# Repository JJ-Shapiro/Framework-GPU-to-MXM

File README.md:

# Framework-GPU-to-MXM
A project to make the first MXM module for the Framework 16.
*Info*
The Framework 16's Expansion bay can't support the size of an MXM module by default, (at least not a type-B module which is bigger than a type a module), but it *can* support it if the back of the GPU expansion slot is pulled out further 

*Disclaimer*
I am not the legal owner of the datasheet describing the footprint of an MXM connector. It is in this repository strictly as a helpful reference for anyone who might desire to use or cross reference it. I will of course remove it at the request of the author.

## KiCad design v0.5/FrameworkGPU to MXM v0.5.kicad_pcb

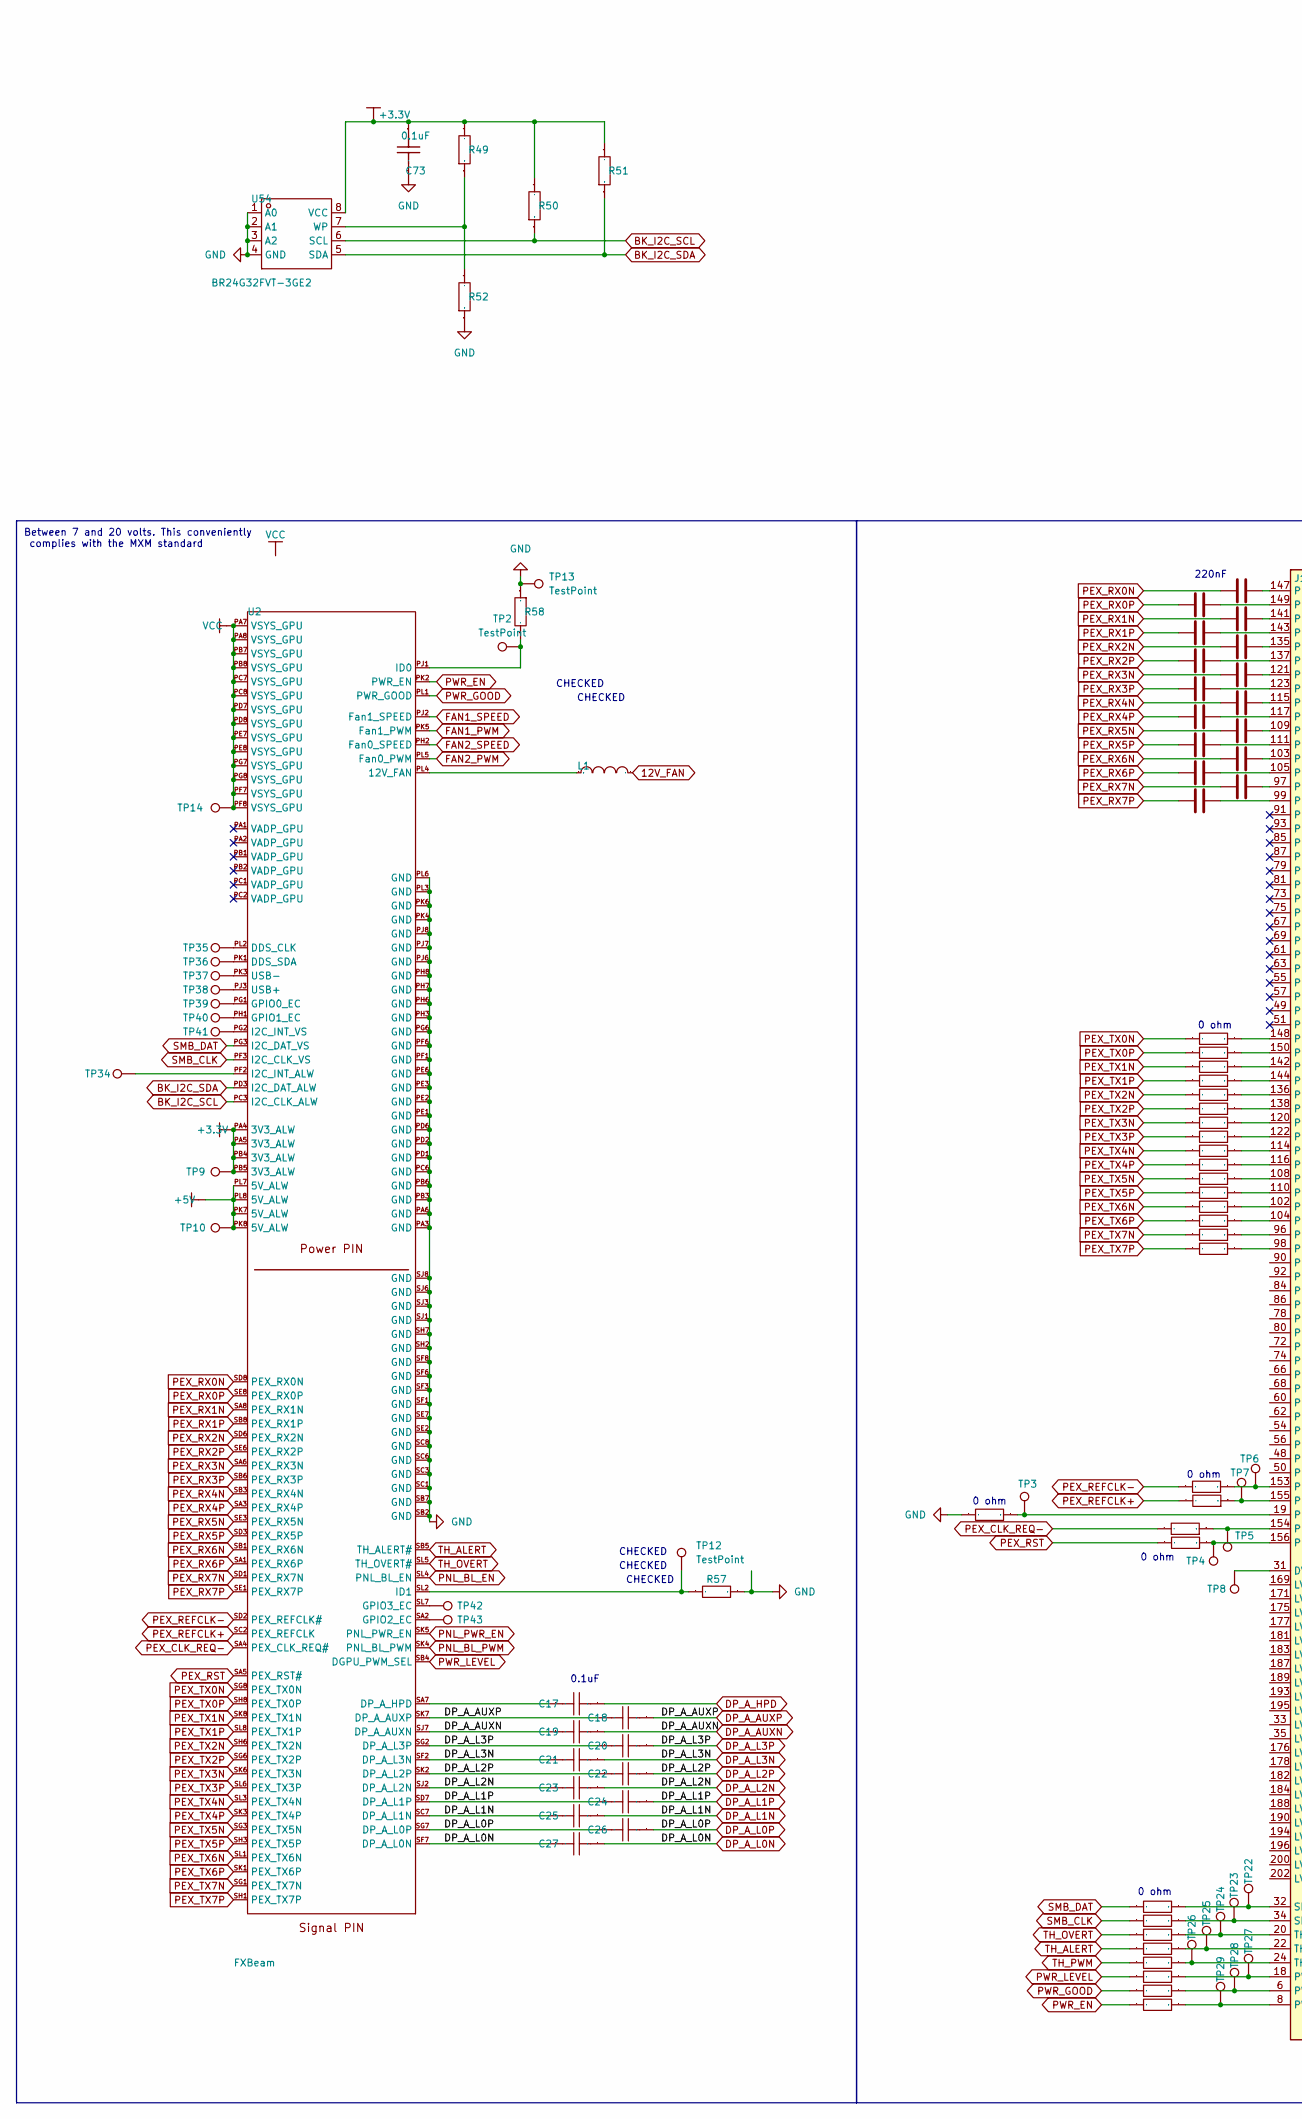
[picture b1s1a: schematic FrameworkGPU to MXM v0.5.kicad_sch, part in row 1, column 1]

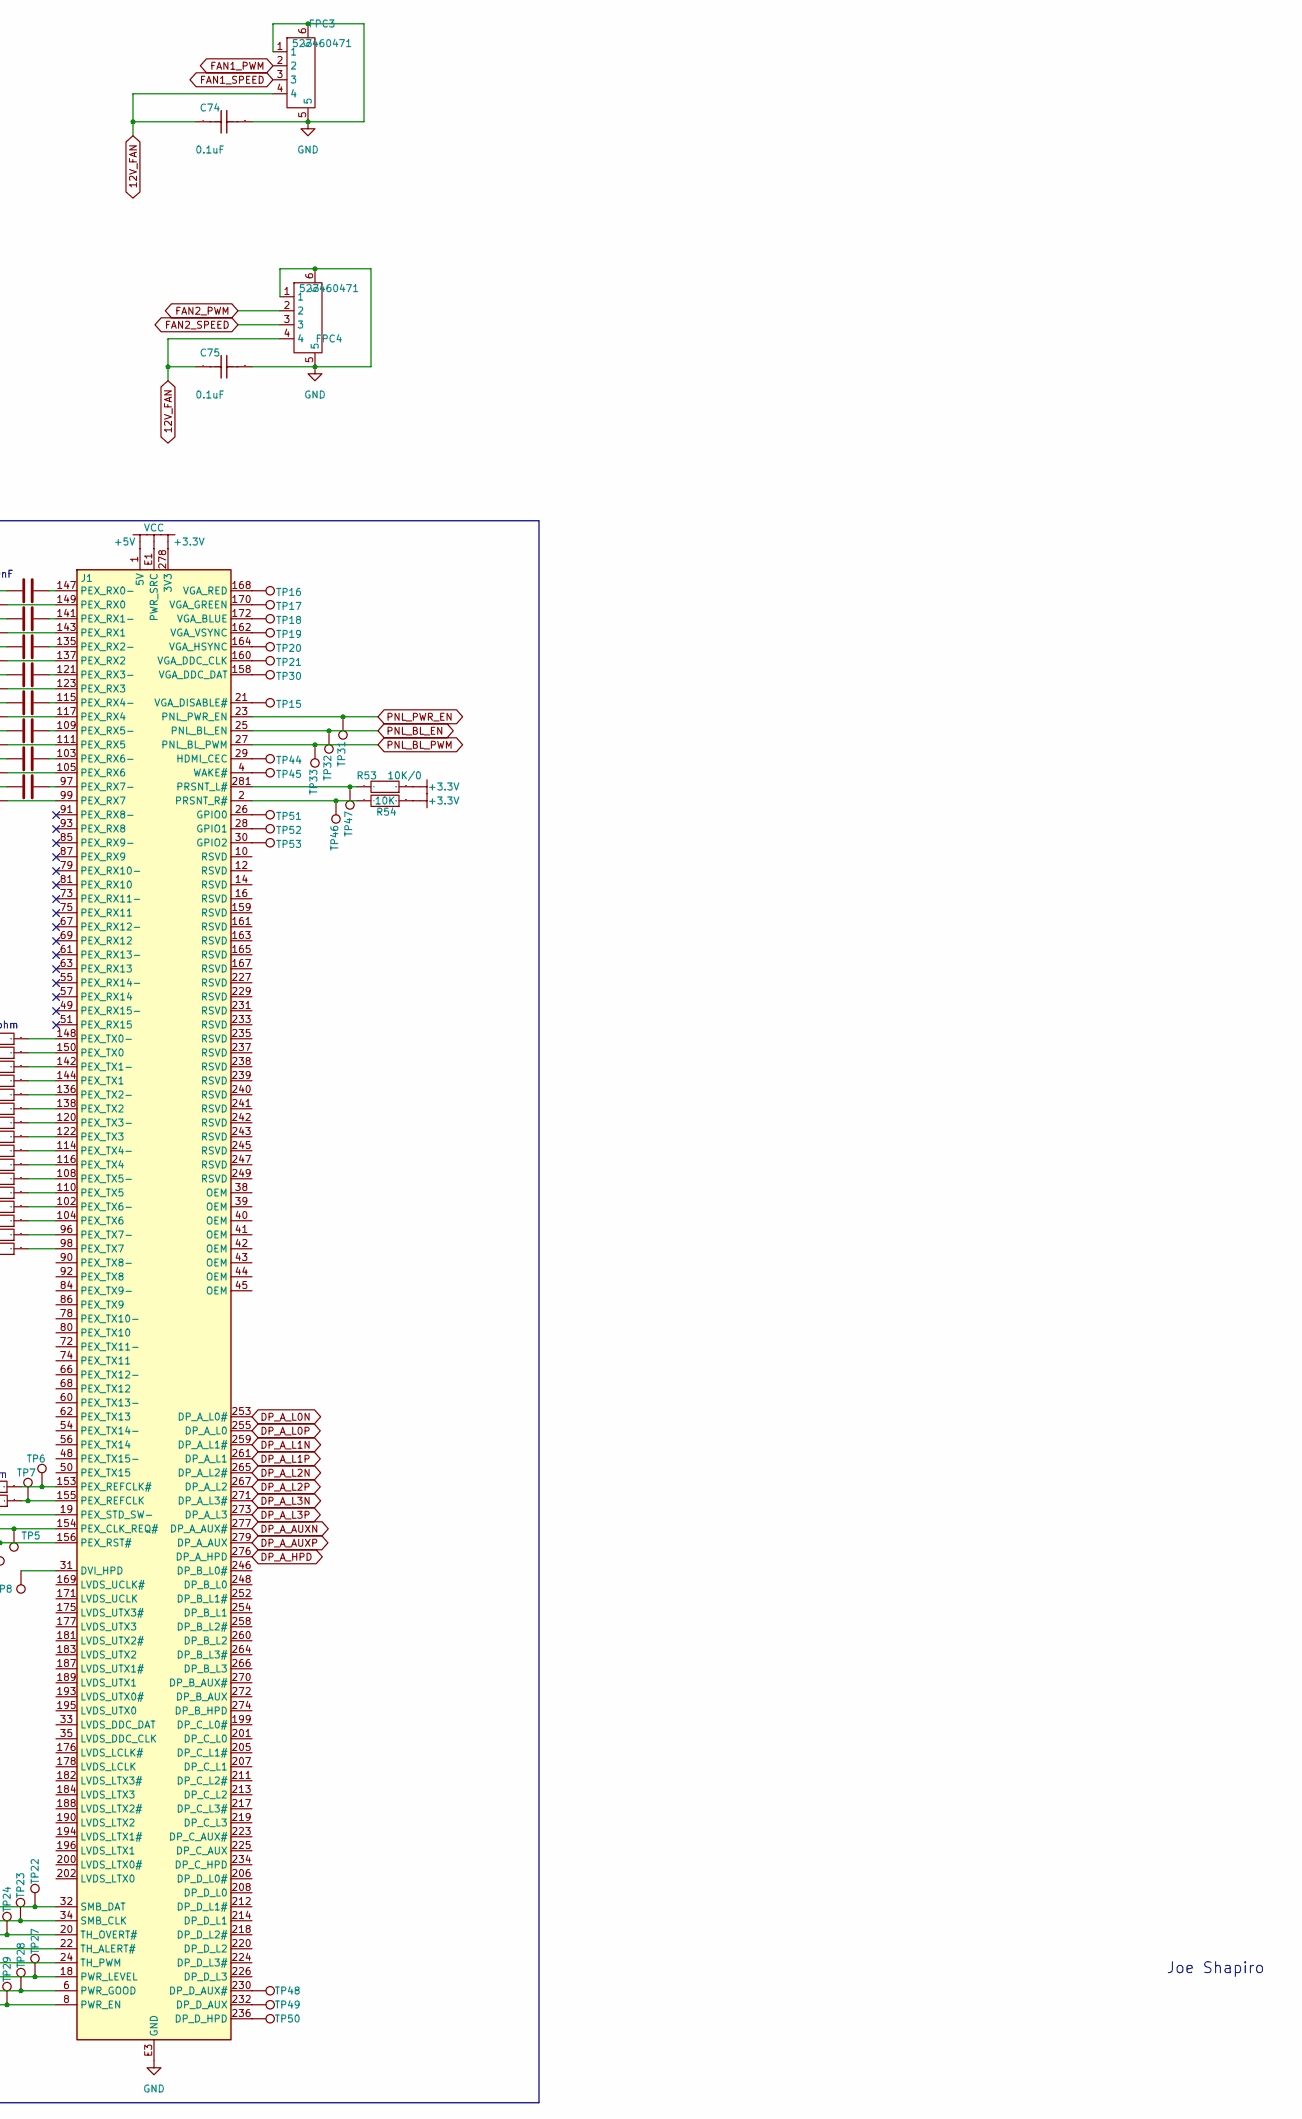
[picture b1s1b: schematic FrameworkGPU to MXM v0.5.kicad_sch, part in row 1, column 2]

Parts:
C1, C2, C3, C4, C5, C6, C7, C8, C9, C10, C11, C12, C13, C14, C15, C16: 220nF; 0603
C17, C18, C19, C20, C21, C22, C23, C24, C25, C26, C27: 100nF; 0603
C73, C74, C75: 0.1uF; 0603
FPC3, FPC4: 527460471; FPC-SMD_4P-P0.50_MOLEX_0527460471; Manufacturer Part 527460471; LCSC Part Name 527460471
J1: MXM3.0; FOXCONN_AS0B826-S55B-7H
L1: 10uH; 0603
R17, R18, R19, R20, R21, R22, R23, R24, R25, R26, R27, R28, R29, R30, R31, R32, R33, R34, R35, R36, R37, R55, R56, R59, R60, R61, R62, R63, R64: 0; 0603
R49, R54: 10K; 0603
R50, R51: 4.7K; 0603
R52: 100K; 0603
R53: 10K/0; 0603
R57, R58: 330K; 0603
TP2, TP3, TP4, TP5, TP6, TP7, TP8, TP9, TP10, TP12, TP13, TP14, TP15, TP16, TP17, TP18, TP19, TP20, TP21, TP22, TP23, TP24, TP25, TP26, TP27, TP28, TP29, TP30, TP31, TP32, TP33, TP34, TP35, TP36, TP37, TP38, TP39, TP40, TP41, TP42, TP43, TP44, TP45, TP46, TP47, TP48, TP49, TP50, TP51, TP52, TP53: TestPoint; TestPoint_Pad_D3.0mm
U2: FXBeam; Expansion Bay FXBeam
U54: BR24G32FVT-3GE2; SOP65P640X120-8N; Manufacturer Part BR24G32FVT-3GE2; LCSC Part Name BR24G32FVT-3GE2

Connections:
+3.3V: C73.1, J1.278 (3V3), J1.280 (3V3), R49.2, R50.2, R51.2, R53.1, R54.1, TP9.1, U2.PA4 (3V3_ALW), U2.PA5 (3V3_ALW), U2.PB4 (3V3_ALW), U2.PB5 (3V3_ALW), U54.8 (VCC)
+5V: J1.1 (5V), J1.3 (5V), J1.5 (5V), J1.7 (5V), J1.9 (5V), TP10.1, U2.PK7 (5V_ALW), U2.PK8 (5V_ALW), U2.PL7 (5V_ALW), U2.PL8 (5V_ALW)
BK_I2C_SCL: R50.1, U2.PC3 (I2C_CLK_ALW), U54.6 (SCL)
BK_I2C_SDA: R51.1, U2.PD3 (I2C_DAT_ALW), U54.5 (SDA)
DP_A_AUXN: C19.1, C19.2, J1.277 (DP_A_AUX#), U2.SJ7 (DP_A_AUXN)
DP_A_AUXP: C18.1, C18.2, J1.279 (DP_A_AUX), U2.SK7 (DP_A_AUXP)
DP_A_HPD: C17.1, J1.276 (DP_A_HPD)
DP_A_L0N: C27.1, C27.2, J1.253 (DP_A_L0#), U2.SF7 (DP_A_L0N)
DP_A_L0P: C26.1, C26.2, J1.255 (DP_A_L0), U2.SG7 (DP_A_L0P)
DP_A_L1N: C25.1, C25.2, J1.259 (DP_A_L1#), U2.SC7 (DP_A_L1N)
DP_A_L1P: C24.1, C24.2, J1.261 (DP_A_L1), U2.SD7 (DP_A_L1P)
DP_A_L2N: C23.1, C23.2, J1.265 (DP_A_L2#), U2.SJ2 (DP_A_L2N)
DP_A_L2P: C22.1, C22.2, J1.267 (DP_A_L2), U2.SK2 (DP_A_L2P)
DP_A_L3N: C21.1, C21.2, J1.271 (DP_A_L3#), U2.SF2 (DP_A_L3N)
DP_A_L3P: C20.1, C20.2, J1.273 (DP_A_L3), U2.SG2 (DP_A_L3P)
FAN1_PWM: FPC3.2, U2.PK5 (Fan1_PWM)
FAN1_SPEED: FPC3.3, U2.PJ2 (Fan1_SPEED)
FAN2_PWM: FPC4.2, U2.PL5 (Fan0_PWM)
FAN2_SPEED: FPC4.3, U2.PH2 (Fan0_SPEED)
GND: C73.2, C74.1, C75.1, FPC3.1, FPC3.5, FPC3.6, FPC4.1, FPC4.5, FPC4.6, J1.11 (GND), J1.13 (GND), J1.15 (GND), J1.17 (GND), J1.36 (GND), J1.37 (GND), J1.46 (GND), J1.47 (GND), J1.52 (GND), J1.53 (GND), J1.58 (GND), J1.59 (GND), J1.64 (GND), J1.65 (GND), J1.70 (GND), J1.71 (GND), J1.76 (GND), J1.77 (GND), J1.82 (GND), J1.83 (GND), J1.88 (GND), J1.89 (GND), J1.94 (GND), J1.95 (GND), J1.100 (GND), J1.101 (GND), J1.106 (GND), J1.107 (GND), J1.112 (GND), J1.113 (GND), J1.118 (GND), J1.119 (GND), J1.124 (GND), J1.125 (GND), J1.133 (GND), J1.134 (GND), J1.139 (GND), J1.140 (GND), J1.145 (GND), J1.146 (GND), J1.151 (GND), J1.152 (GND), J1.157 (GND), J1.166 (GND), J1.173 (GND), J1.174 (GND), J1.179 (GND), J1.180 (GND), J1.185 (GND), J1.186 (GND), J1.191 (GND), J1.192 (GND), J1.197 (GND), J1.198 (GND), J1.203 (GND), J1.204 (GND), J1.209 (GND), J1.210 (GND), J1.215 (GND), J1.216 (GND), J1.221 (GND), J1.222 (GND), J1.228 (GND), J1.244 (GND), J1.250 (GND), J1.251 (GND), J1.256 (GND), J1.257 (GND), J1.262 (GND), J1.263 (GND), J1.268 (GND), J1.269 (GND), J1.275 (GND), J1.E3 (GND), J1.E4 (GND), R33.2, R52.1, R57.1, R58.1, TP13.1, U2.PA3 (GND), U2.PA6 (GND), U2.PB3 (GND), U2.PB6 (GND), U2.PC6 (GND), U2.PD1 (GND), U2.PD2 (GND), U2.PD6 (GND), U2.PE1 (GND), U2.PE2 (GND), U2.PE3 (GND), U2.PE6 (GND), U2.PF1 (GND), U2.PF6 (GND), U2.PG6 (GND), U2.PH3 (GND), U2.PH6 (GND), U2.PH7 (GND), U2.PH8 (GND), U2.PJ6 (GND), U2.PJ7 (GND), U2.PJ8 (GND), U2.PK4 (GND), U2.PK6 (GND), U2.PL3 (GND), U2.PL6 (GND), U2.SB2 (GND), U2.SB7 (GND), U2.SC1 (GND), U2.SC3 (GND), U2.SC6 (GND), U2.SC8 (GND), U2.SE2 (GND), U2.SE7 (GND), U2.SF1 (GND), U2.SF3 (GND), U2.SF6 (GND), U2.SF8 (GND), U2.SH2 (GND), U2.SH7 (GND), U2.SJ1 (GND), U2.SJ3 (GND), U2.SJ6 (GND), U2.SJ8 (GND), U54.1 (A0), U54.2 (A1), U54.3 (A2), U54.4 (GND)
unnamed: C74.2, C75.2, FPC3.4, FPC4.4, L1.2
unnamed: J1.230 (DP_D_AUX#), TP48.1
unnamed: J1.232 (DP_D_AUX), TP49.1
unnamed: J1.236 (DP_D_HPD), TP50.1
unnamed: J1.31 (DVI_HPD), TP8.1
unnamed: J1.26 (GPIO0), TP51.1
unnamed: J1.28 (GPIO1), TP52.1
unnamed: J1.30 (GPIO2), TP53.1
unnamed: J1.29 (HDMI_CEC), TP44.1
unnamed: J1.154 (PEX_CLK_REQ#), R35.1, TP5.1
unnamed: J1.153 (PEX_REFCLK#), R36.1, TP6.1
unnamed: J1.155 (PEX_REFCLK), R37.1, TP7.1
unnamed: J1.156 (PEX_RST#), R34.1, TP4.1
unnamed: C1.1, J1.149 (PEX_RX0)
unnamed: C9.1, J1.147 (PEX_RX0-)
unnamed: C2.1, J1.143 (PEX_RX1)
unnamed: C10.1, J1.141 (PEX_RX1-)
unnamed: C3.1, J1.137 (PEX_RX2)
unnamed: C11.1, J1.135 (PEX_RX2-)
unnamed: C4.1, J1.123 (PEX_RX3)
unnamed: C12.1, J1.121 (PEX_RX3-)
unnamed: C5.1, J1.117 (PEX_RX4)
unnamed: C13.1, J1.115 (PEX_RX4-)
unnamed: C6.1, J1.111 (PEX_RX5)
unnamed: C14.1, J1.109 (PEX_RX5-)
unnamed: C7.1, J1.105 (PEX_RX6)
unnamed: C15.1, J1.103 (PEX_RX6-)
unnamed: C8.1, J1.99 (PEX_RX7)
unnamed: C16.1, J1.97 (PEX_RX7-)
unnamed: J1.19 (PEX_STD_SW-), R33.1, TP3.1
unnamed: J1.150 (PEX_TX0), R18.1
unnamed: J1.148 (PEX_TX0-), R17.1
unnamed: J1.144 (PEX_TX1), R20.1
unnamed: J1.142 (PEX_TX1-), R19.1
unnamed: J1.138 (PEX_TX2), R22.1
unnamed: J1.136 (PEX_TX2-), R21.1
unnamed: J1.122 (PEX_TX3), R24.1
unnamed: J1.120 (PEX_TX3-), R23.1
unnamed: J1.116 (PEX_TX4), R26.1
unnamed: J1.114 (PEX_TX4-), R25.1
unnamed: J1.110 (PEX_TX5), R28.1
unnamed: J1.108 (PEX_TX5-), R27.1
unnamed: J1.104 (PEX_TX6), R30.1
unnamed: J1.102 (PEX_TX6-), R29.1
unnamed: J1.98 (PEX_TX7), R32.1
unnamed: J1.96 (PEX_TX7-), R31.1
unnamed: J1.281 (PRSNT_L#), R53.2, TP47.1
unnamed: J1.2 (PRSNT_R#), R54.2, TP46.1
unnamed: J1.8 (PWR_EN), R64.1, TP29.1
unnamed: J1.6 (PWR_GOOD), R63.1, TP28.1
unnamed: J1.18 (PWR_LEVEL), R62.1, TP27.1
unnamed: J1.34 (SMB_CLK), R56.1, TP23.1
unnamed: J1.32 (SMB_DAT), R55.1, TP22.1
unnamed: J1.22 (TH_ALERT#), R60.1, TP25.1
unnamed: J1.20 (TH_OVERT#), R59.1, TP24.1
unnamed: J1.24 (TH_PWM), R61.1, TP26.1
unnamed: J1.172 (VGA_BLUE), TP18.1
unnamed: J1.160 (VGA_DDC_CLK), TP21.1
unnamed: J1.158 (VGA_DDC_DAT), TP30.1
unnamed: J1.21 (VGA_DISABLE#), TP15.1
unnamed: J1.170 (VGA_GREEN), TP17.1
unnamed: J1.164 (VGA_HSYNC), TP20.1
unnamed: J1.168 (VGA_RED), TP16.1
unnamed: J1.162 (VGA_VSYNC), TP19.1
unnamed: J1.4 (WAKE#), TP45.1
unnamed: L1.1, U2.PL4 (12V_FAN)
unnamed: TP35.1, U2.PL2 (DDS_CLK)
unnamed: TP36.1, U2.PK1 (DDS_SDA)
unnamed: C17.2, U2.SA7 (DP_A_HPD)
unnamed: TP39.1, U2.PG1 (GPIO0_EC)
unnamed: TP40.1, U2.PH1 (GPIO1_EC)
unnamed: TP43.1, U2.SA2 (GPIO2_EC)
unnamed: TP42.1, U2.SL7 (GPIO3_EC)
unnamed: TP34.1, U2.PF2 (I2C_INT_ALW)
unnamed: TP41.1, U2.PG2 (I2C_INT_VS)
unnamed: R58.2, TP2.1, U2.PJ1 (ID0)
unnamed: R57.2, TP12.1, U2.SL2 (ID1)
unnamed: TP38.1, U2.PJ3 (USB+)
unnamed: TP37.1, U2.PK3 (USB-)
unnamed: R49.1, R52.2, U54.7 (WP)
PEX_CLK_REQ-: R35.2, U2.SA4 (PEX_CLK_REQ#)
PEX_REFCLK+: R37.2, U2.SC2 (PEX_REFCLK)
PEX_REFCLK-: R36.2, U2.SD2 (PEX_REFCLK#)
PEX_RST: R34.2, U2.SA5 (PEX_RST#)
PEX_RX0N: C9.2, U2.SD8 (PEX_RX0N)
PEX_RX0P: C1.2, U2.SE8 (PEX_RX0P)
PEX_RX1N: C10.2, U2.SA8 (PEX_RX1N)
PEX_RX1P: C2.2, U2.SB8 (PEX_RX1P)
PEX_RX2N: C11.2, U2.SD6 (PEX_RX2N)
PEX_RX2P: C3.2, U2.SE6 (PEX_RX2P)
PEX_RX3N: C12.2, U2.SA6 (PEX_RX3N)
PEX_RX3P: C4.2, U2.SB6 (PEX_RX3P)
PEX_RX4N: C13.2, U2.SB3 (PEX_RX4N)
PEX_RX4P: C5.2, U2.SA3 (PEX_RX4P)
PEX_RX5N: C14.2, U2.SE3 (PEX_RX5N)
PEX_RX5P: C6.2, U2.SD3 (PEX_RX5P)
PEX_RX6N: C15.2, U2.SB1 (PEX_RX6N)
PEX_RX6P: C7.2, U2.SA1 (PEX_RX6P)
PEX_RX7N: C16.2, U2.SD1 (PEX_RX7N)
PEX_RX7P: C8.2, U2.SE1 (PEX_RX7P)
PEX_TX0N: R17.2, U2.SG8 (PEX_TX0N)
PEX_TX0P: R18.2, U2.SH8 (PEX_TX0P)
PEX_TX1N: R19.2, U2.SK8 (PEX_TX1N)
PEX_TX1P: R20.2, U2.SL8 (PEX_TX1P)
PEX_TX2N: R21.2, U2.SH6 (PEX_TX2N)
PEX_TX2P: R22.2, U2.SG6 (PEX_TX2P)
PEX_TX3N: R23.2, U2.SK6 (PEX_TX3N)
PEX_TX3P: R24.2, U2.SL6 (PEX_TX3P)
PEX_TX4N: R25.2, U2.SL3 (PEX_TX4N)
PEX_TX4P: R26.2, U2.SK3 (PEX_TX4P)
PEX_TX5N: R27.2, U2.SG3 (PEX_TX5N)
PEX_TX5P: R28.2, U2.SH3 (PEX_TX5P)
PEX_TX6N: R29.2, U2.SL1 (PEX_TX6N)
PEX_TX6P: R30.2, U2.SK1 (PEX_TX6P)
PEX_TX7N: R31.2, U2.SG1 (PEX_TX7N)
PEX_TX7P: R32.2, U2.SH1 (PEX_TX7P)
PNL_BL_EN: J1.25 (PNL_BL_EN), TP32.1, U2.SL4 (PNL_BL_EN)
PNL_BL_PWM: J1.27 (PNL_BL_PWM), TP33.1, U2.SK4 (PNL_BL_PWM)
PNL_PWR_EN: J1.23 (PNL_PWR_EN), TP31.1, U2.SK5 (PNL_PWR_EN)
PWR_EN: R64.2, U2.PK2 (PWR_EN)
PWR_GOOD: R63.2, U2.PL1 (PWR_GOOD)
PWR_LEVEL: R62.2, U2.SB4 (DGPU_PWM_SEL)
SMB_CLK: R56.2, U2.PF3 (I2C_CLK_VS)
SMB_DAT: R55.2, U2.PG3 (I2C_DAT_VS)
TH_ALERT: R60.2, U2.SB5 (TH_ALERT#)
TH_OVERT: R59.2, U2.SL5 (TH_OVERT#)
TH_PWM: R61.2
VCC: J1.E1 (PWR_SRC), J1.E2 (PWR_SRC), TP14.1, U2.PA7 (VSYS_GPU), U2.PA8 (VSYS_GPU), U2.PB7 (VSYS_GPU), U2.PB8 (VSYS_GPU), U2.PC7 (VSYS_GPU), U2.PC8 (VSYS_GPU), U2.PD7 (VSYS_GPU), U2.PD8 (VSYS_GPU), U2.PE7 (VSYS_GPU), U2.PE8 (VSYS_GPU), U2.PF7 (VSYS_GPU), U2.PF8 (VSYS_GPU), U2.PG7 (VSYS_GPU), U2.PG8 (VSYS_GPU)

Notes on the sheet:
0 ohm
CHECKED
0.1uF
Joe Shapiro
Between 7 and 20 volts. This conveniently complies with the MXM standard
220nF

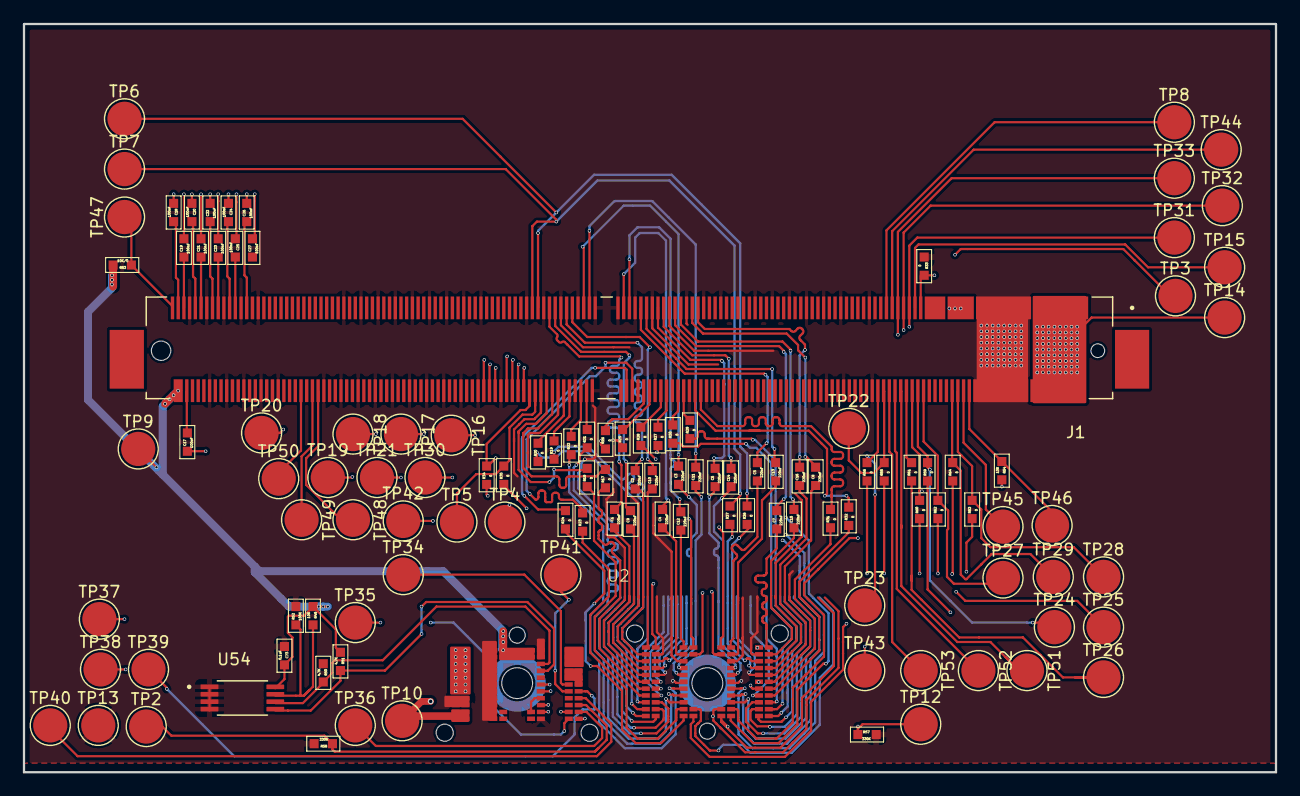
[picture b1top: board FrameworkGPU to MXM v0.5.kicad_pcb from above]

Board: 6 copper layers, 109.6 x 65.5 mm, 119 parts (0 on the bottom side), 141 nets.

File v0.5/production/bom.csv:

Designator,Footprint,Quantity,Value,LCSC Part #
"C1, C10, C11, C12, C13, C14, C15, C16, C2, C3, C4, C5, C6, C7, C8, C9",0603,16,220nF,
"C17, C18, C19, C20, C21, C22, C23, C24, C25, C26, C27",0603,11,100nF,
C73,0603,1,0.1uF,
J1,FOXCONN_AS0B826-S55B-7H,1,MXM3.0,
"R17, R18, R19, R20, R21, R22, R23, R24, R25, R26, R27, R28, R29, R30, R31, R32, R33, R34, R35, R36, R37, R55, R56, R59, R60, R61, R62, R63, R64",0603,29,0,
"R49, R54",0603,2,10K,
"R50, R51",0603,2,4.7K,
R52,0603,1,100K,
R53,0603,1,10K/0,
"R57, R58",0603,2,330K,
"TP10, TP12, TP13, TP14, TP15, TP16, TP17, TP18, TP19, TP2, TP20, TP21, TP22, TP23, TP24, TP25, TP26, TP27, TP28, TP29, TP3, TP30, TP31, TP32, TP33, TP34, TP35, TP36, TP37, TP38, TP39, TP4, TP40, TP41, TP42, TP43, TP44, TP45, TP46, TP47, TP48, TP49, TP5, TP50, TP51, TP52, TP53, TP6, TP7, TP8, TP9",TestPoint_Pad_D3.0mm,51,TestPoint,
U2,Expansion Bay FXBeam,1,FXBeam,
U54,SOP65P640X120-8N,1,BR24G32FVT-3GE2,

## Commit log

2025-08-19 Added V0.2 Files
2025-08-19 Rename FrameworkGPU to MXM.epro to V0.1/FrameworkGPU to MXM.epro
2025-08-19 Rename Bottom Assembly Drawings.pdf to Bottom Assembly Drawings.pdf
2025-08-19 Rename Drill Drawing.pdf to Drill Drawing.pdf
2025-08-19 Rename Top Assembly Drawings.pdf to Top Assembly Drawings.pdf
2025-08-19 Rename FrameworkGPU to MXM V0.2_2025-08-19.epro to V0.2/FrameworkGPU to MXM V0.2_2025-08-19.epro
2025-08-20 Rename FrameworkGPU to MXM V0.3.epro to V0.3/FrameworkGPU to MXM V0.3.epro
2025-08-21 Rename FrameworkGPU to MXM V0.4.epro to V0.4/FrameworkGPU to MXM V0.4.epro
2025-08-23 Rename FrameworkGPU to MXM V0.31.epro to V0.31/FrameworkGPU to MXM V0.31.epro
2025-09-18 Added V3.2
    Fixed incorrect PCIE orientation
2025-09-18 Rename FrameworkGPU to MXM V3.2.epro to V3.2/FrameworkGPU to MXM V3.2.epro
2025-09-22 V3.3 Added
    Fixed fan headers and completed length matching
2025-09-22 Rename FrameworkGPU to MXM V3.3.epro to V3.3/FrameworkGPU to MXM V3.3.epro
2025-09-28 Create Datasheets
2025-09-28 Rename MXM Schematic Footprint.pdf to Datasheets/MXM Schematic Footprint.pdf
2025-11-28 Rename FrameworkGPU to MXM v0.34.epro to v0.34/FrameworkGPU to MXM v0.34.epro
2025-11-28 Rename FrameworkGPU to MXM V3.3.epro to FrameworkGPU to MXM V3.3.epro
2025-11-28 Rename V3.2/FrameworkGPU to MXM V3.2.epro to V0.32FrameworkGPU to MXM V3.2.epro
2025-11-28 Rename V0.32FrameworkGPU to MXM V3.2.epro to v0.32/FrameworkGPU to MXM V3.2.epro
2026-01-25 Update README with additional images and info
2026-03-07 added v0.5
2026-03-07 Diff routed
2026-03-22 committing final version sent off for manufacturing
